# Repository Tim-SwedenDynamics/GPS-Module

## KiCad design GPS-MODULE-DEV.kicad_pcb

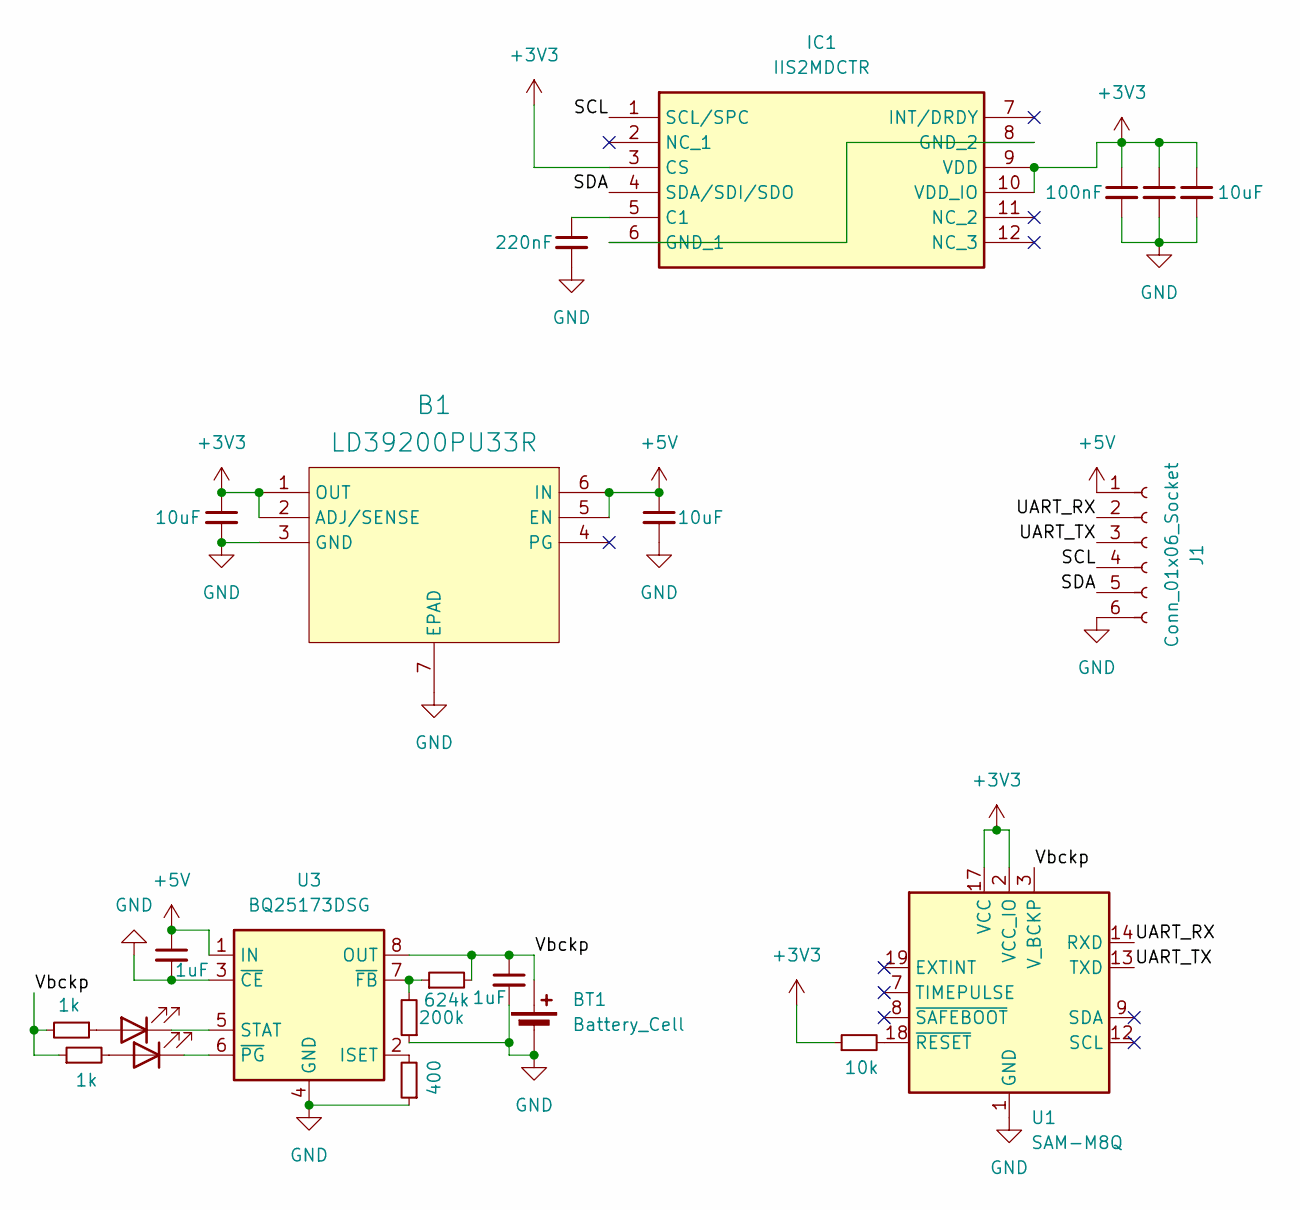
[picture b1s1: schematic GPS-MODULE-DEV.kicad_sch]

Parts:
B1: LD39200PU33R; SON95P300X300X100-7N-D; Manufacturer_Part_Number LD39200PU33R; Mouser Part Number 511-LD39200PU33R
BT1: Battery_Cell; RSCSK2243R3D02008U
C1, C2: 1uF; C_0402_1005Metric
C3, C4, C6: 10uF; C_0402_1005Metric
C5, C7: 100nF; C_0402_1005Metric
C8: 220nF; C_0402_1005Metric
D1, D2: LED; D_0402_1005Metric
IC1: IIS2MDCTR; IIS2MDCTR_v2; Manufacturer_Part_Number IIS2MDCTR; Mouser Part Number 511-IIS2MDCTR
J1: Conn_01x06_Socket; JST_GH_SM06B-GHS-TB_1x06-1MP_P1.25mm_Horizontal
R1: 10k; R_0402_1005Metric
R2: 400; R_0402_1005Metric
R3, R4: 1k; R_0402_1005Metric
R5: 624k; R_0402_1005Metric
R6: 200k; R_0402_1005Metric
U1: SAM-M8Q; ublox_SAM-M8Q
U3: BQ25173DSG; WSON-8-1EP_2x2mm_P0.5mm_EP0.9x1.6mm

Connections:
+3V3: B1.1 (OUT), B1.2 (ADJ/SENSE), C4.1, C5.1, C6.1, C7.1, IC1.3 (CS), IC1.9 (VDD), IC1.10 (VDD_IO), R1.1, U1.2 (VCC_IO), U1.17 (VCC)
+5V: B1.5 (EN), B1.6 (IN), C2.1, C3.1, J1.1, U3.1 (IN)
/SCL: IC1.1 (SCL/SPC), J1.4
/SDA: IC1.4 (SDA/SDI/SDO), J1.5
/UART_RX: J1.2, U1.14 (RXD)
/UART_TX: J1.3, U1.13 (TXD)
/Vbckp: BT1.1 (+), C1.1, R3.1, R4.2, R5.2, U1.3 (V_BCKP), U3.8 (OUT)
GND: B1.3 (GND), B1.7 (EPAD), BT1.2 (-), C1.2, C2.2, C3.2, C4.2, C5.2, C6.2, C7.2, C8.2, J1.6, J1.MP, R2.1, R6.1, U1.1 (GND), U1.4 (GND), U1.5 (GND), U1.6 (GND), U1.10 (GND), U1.11 (GND), U1.15 (GND), U1.16 (GND), U1.20 (GND), U3.3 (~CE), U3.4 (GND), U3.9 (GND)
unnamed: D1.2 (A), R4.1
unnamed: D1.1 (K), U3.5 (STAT)
unnamed: D2.2 (A), R3.2
unnamed: D2.1 (K), U3.6 (~PG)
unnamed: C8.1, IC1.5 (C1)
unnamed: IC1.6 (GND_1), IC1.8 (GND_2)
unnamed: R1.2, U1.18 (~RESET)
unnamed: R2.2, U3.2 (ISET)
unnamed: R5.1, R6.2, U3.7 (~FB)

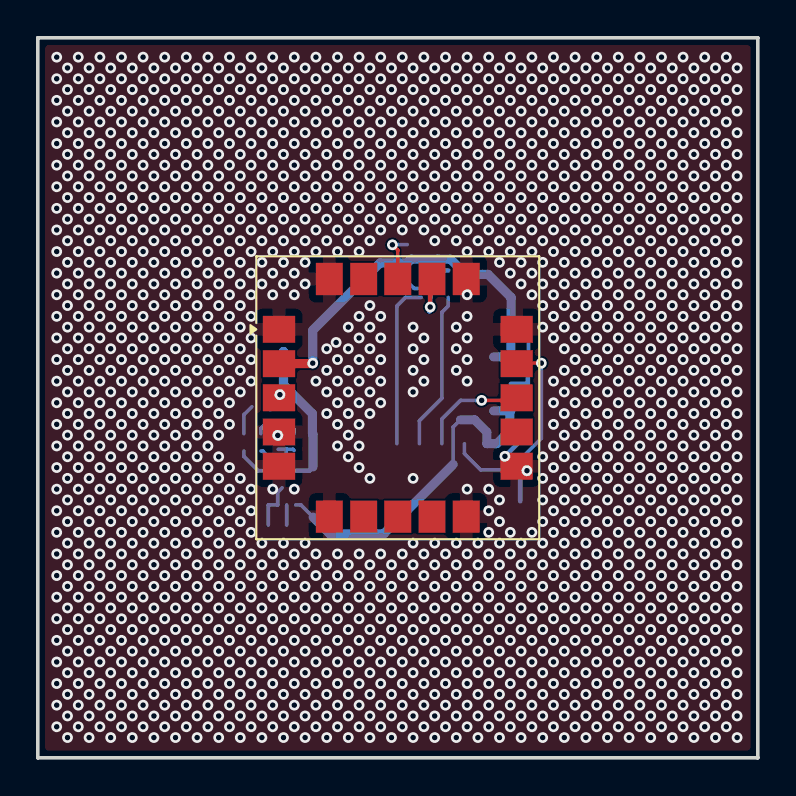
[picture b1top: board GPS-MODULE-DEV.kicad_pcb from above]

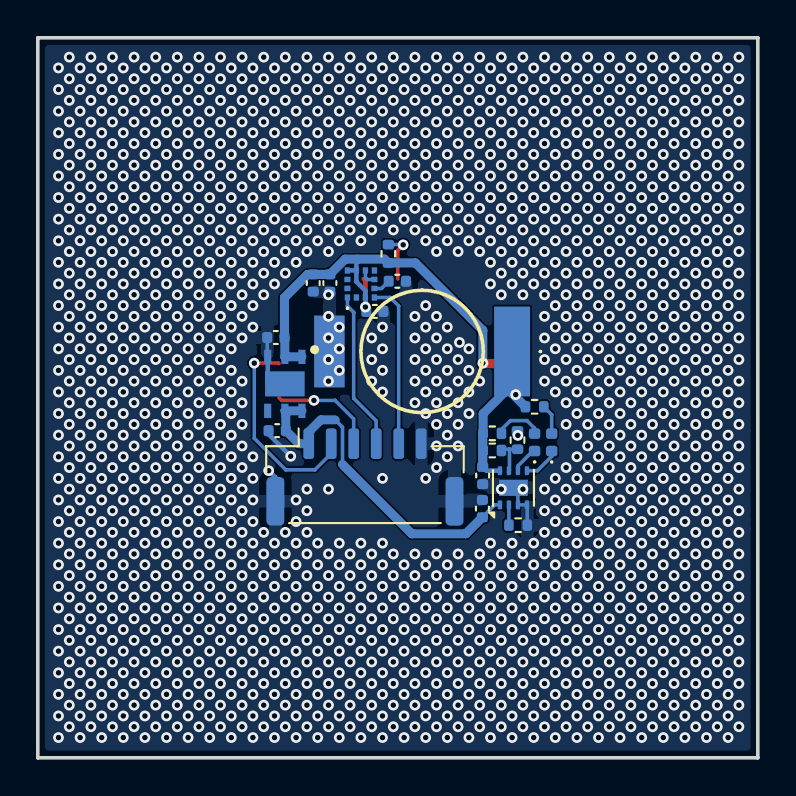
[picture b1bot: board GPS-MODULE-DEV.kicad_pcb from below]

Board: 2 copper layers, 40.0 x 40.0 mm, 22 parts (21 on the bottom side), 17 nets.

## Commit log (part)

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2026-06-11 V1/intial commit
